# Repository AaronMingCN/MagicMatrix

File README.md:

# MagicMatrix 魔法矩阵

## 功能

### 基础功能

+ 时间显示

    ```txt
    显示当前24小时制时间
    ```

+ 日期显示

    ```txt
    显示当前日期
    ```

+ 显示环境温度湿度
  
    ```txt
    显示当前环境的温度和湿度
    ```

+ BMP位图循环显示

  + 将图片放置在SD卡的bmp文件夹下
  + bmp文件必须为24位16x16分辨率图像
  + 向上增减显示间隔500毫秒
  + 向下减少显示间隔500毫秒，最小间隔500毫秒

+ BMP位图静态显示

  + 向左切换前一张图片
  + 向右切换下一张图片

### 扩展功能

+ 倒计时

    ```txt
    向上增加5分钟，向下减少5分钟，向右增加1分钟，向左减少1分钟
    设置完成后按set键开始倒计时，倒计时结束后会响铃提醒
    ```

+ 正计时功能

    ```txt
    向右开始计时，向左停止计时，向下计时归零
    ```

+ 记分牌

    ```txt
    显示比赛双方的分数,通过遥控器来控制分数的增加和减少
    向上增加上方分数，向下增加下方分数
    向左减少上方分数，向右减少下方分数
    ```

+ 投骰子功能

    ```txt
    投骰子功能会从1~6取随机数，支持1~4个骰子
    向上1个骰子，向左2个骰子，向下3个骰子，向右4个骰子
    ```

### 辅助功能

+ 检测周围人体自动节能
+ 使用电池模块可移动使用
+ 断电前状态保存

    ```txt
    断电重启后可返回到断电之前的状态
    ```

+ 开机显示LOGO

### 远程功能

+ 手机蓝牙对时

    ```txt
    通过手机蓝牙APP发送指令可以对设备时间进行矫正
    发送指令格式：MM SDT 2024 03 15 00 00 00
    含义：MagicMatrix SetDateTime 2024-03-15 00:00:00
    ```

+ 手机切换当前功能
  
    ```txt
    通过手机蓝牙APP可切换设备当前正在执行的功能
    发送指令格式：MM MENU 0 0
    含义：MagicMatrix Menu 0 0
    ```

## 后期扩展功能

+ wifi自动校时功能
+ 根据环境光自动调整工作亮度
+ 手机屏幕矩阵绘制
+ 留言功能
+ 环境声音频谱显示
+ 闹钟设置
+ 五子棋游戏
+ 贪食蛇游戏
+ 俄罗斯方块游戏

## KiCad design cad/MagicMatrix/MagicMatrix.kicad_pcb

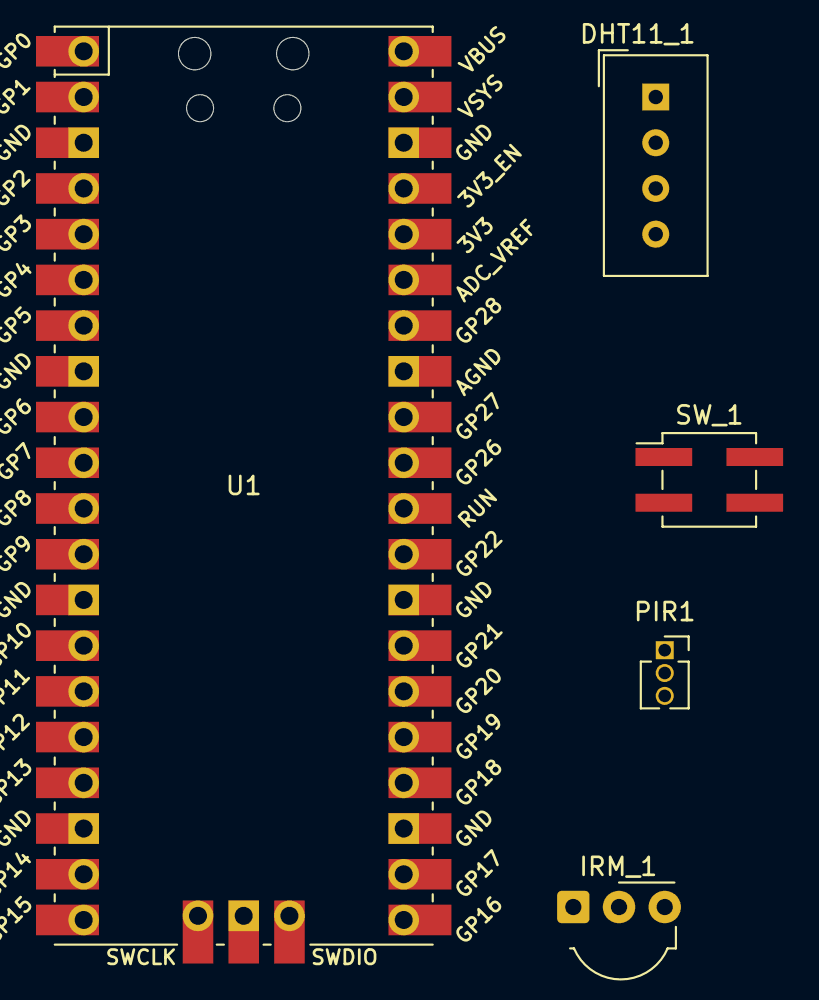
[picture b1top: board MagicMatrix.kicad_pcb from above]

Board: 2 copper layers, 5 parts (0 on the bottom side), 6 nets, no tracks yet.

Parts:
DHT11_1: 温湿度传感器; Aosong_DHT11_5.5x12.0_P2.54mm
IRM_1: 红外线接收模块; Vishay_MOLD-3Pin
PIR1: 红外线人体探测模块; PinSocket_1x03_P1.27mm_Vertical
SW_1: Reset; PinHeader_2x02_P2.54mm_Vertical_SMD
U1: Raspberry Pi Pico; RPi_Pico_SMD_TH

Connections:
/GPIO7: PIR1.2 (OUT), U1.10 (GPIO7)
/GPIO21: DHT11_1.2 (DATA), U1.27 (GPIO21)
/GPIO22: IRM_1.1 (OUT), U1.29 (GPIO22)
/RUN: SW_1.1, U1.30 (RUN)
/VSYS: DHT11_1.1 (VDD), IRM_1.2 (Vs), PIR1.1 (VDD), U1.39 (VSYS)
GNDREF: DHT11_1.4 (GND), IRM_1.3 (GND), PIR1.3 (GND), SW_1.2, U1.38 (GND)

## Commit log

2024-02-11 add ubuntu
2024-02-11 test
2024-02-11 Refactor
2024-02-14 add function pool
2024-02-24 udpate
2024-02-28 Change to DS1307
2024-03-26 refacing
2025-01-13 删除 VSCode 设置文件
